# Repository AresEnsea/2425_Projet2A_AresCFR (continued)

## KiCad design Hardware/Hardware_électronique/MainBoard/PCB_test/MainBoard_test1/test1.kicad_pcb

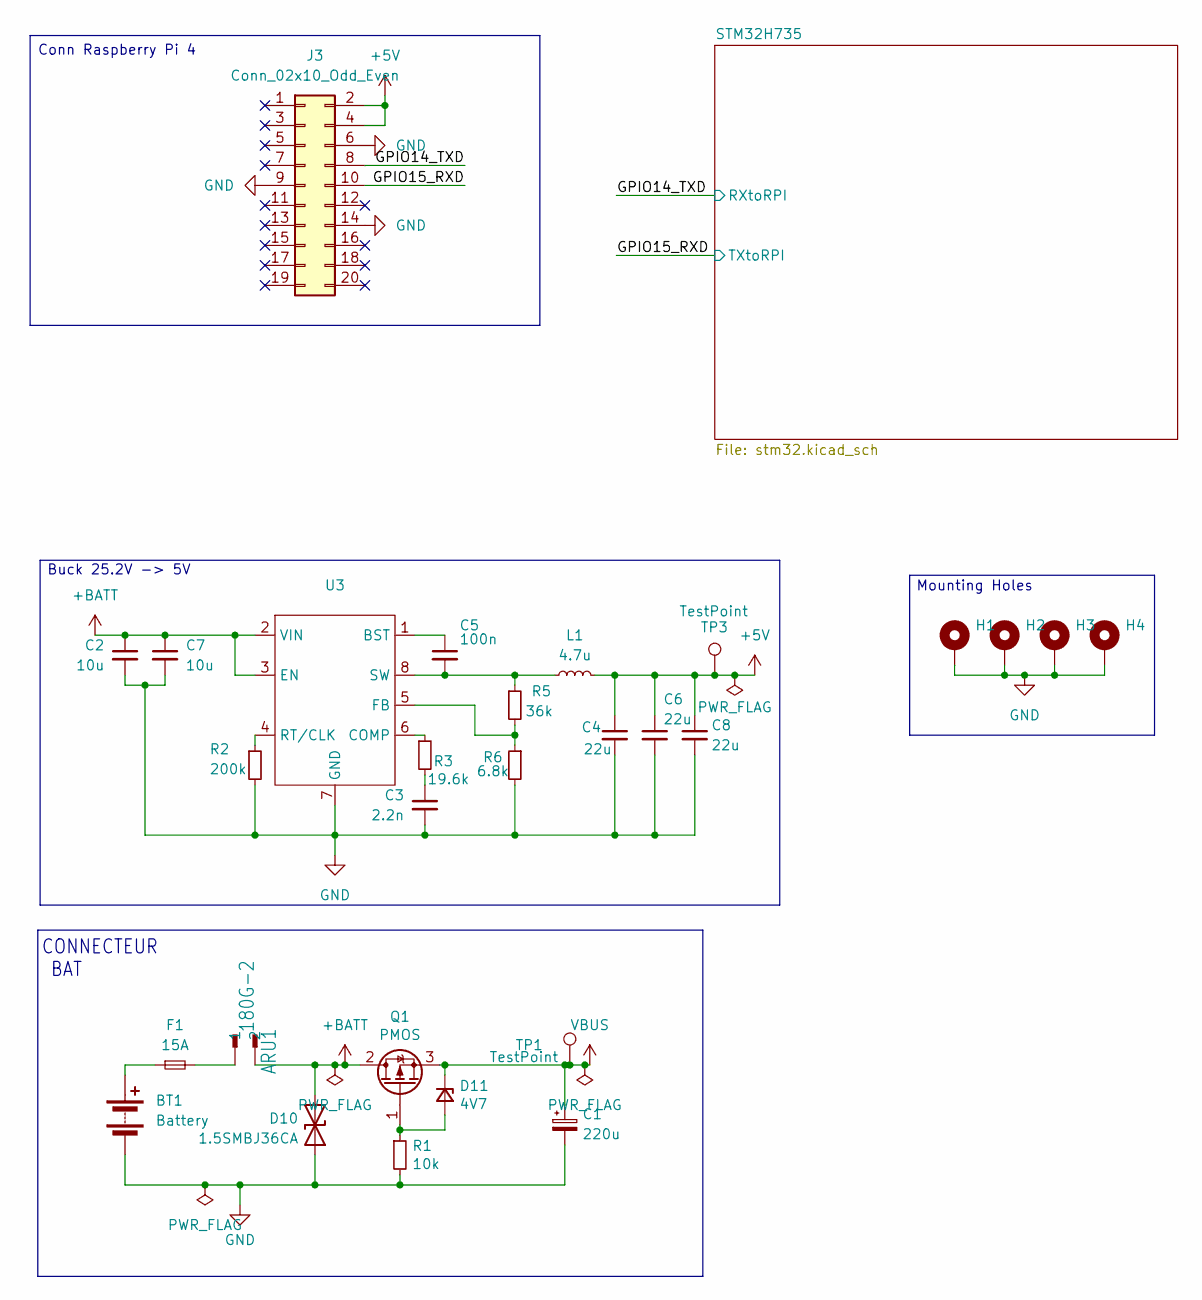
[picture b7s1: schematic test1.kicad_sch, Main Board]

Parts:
ARU1: 180G-2
BT1: Battery; AMASS_XT60PW-F_1x02_P7.20mm_Horizontal
C1: 220u; CP_Elec_10x10.5
C2, C7: 10u; C_0805_2012Metric
C3: 2.2n; C_0402_1005Metric
C4, C6, C8: 22u; C_0402_1005Metric
C5: 100n; C_0402_1005Metric
D10: 1.5SMBJ36CA; D_SMB; Mouser Part Number 652-1.5SMBJ36CA-H
D11: 4V7; D_0603_1608Metric; Mouser Part Number 771-BZX84J-C4V7115
F1: 15A; Fuse_1206_3216Metric
H1, H2, H3, H4: MountingHole_Pad; MountingHole_2.7mm_M2.5
J3: Conn_02x10_Odd_Even; PinSocket_2x10_P2.54mm_Vertical
L1: 4.7u; PA5432.472NLT; MPN 74404084220
Q1: PMOS; MOS_WDFN8; Mouser Part Number 863-NTTFS015P03P8ZWG
R1: 10k; R_0402_1005Metric
R2: 200k; R_0402_1005Metric
R3: 19.6k; R_0402_1005Metric
R5: 36k; R_0402_1005Metric
R6: 6.8k; R_0402_1005Metric
TP1, TP3: TestPoint; TestPoint_Pad_D2.0mm
U3: SOIC-8-1EP_3.9x4.9mm_P1.27mm_EP2.95x4.9mm_Mask2.71x3.4mm

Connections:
+5V: C4.1, C6.1, C8.1, J3.2, J3.4, L1.2, TP3.1; also elsewhere on the board
+BATT: ARU1.2, C2.1, C7.1, D10.2 (A2), Q1.2 (D), U3.2 (VIN), U3.3 (EN)
/GPIO14_TXD: J3.8; also elsewhere on the board
/GPIO15_RXD: J3.10; also elsewhere on the board
GND: BT1.2 (-), C1.2, C2.2, C3.2, C4.2, C6.2, C7.2, C8.2, D10.1 (A1), H1.1, H2.1, H3.1, H4.1, J3.6, J3.9, J3.14, R1.2, R2.2, R6.2, U3.7 (GND), U3.9 (EPad); also elsewhere on the board
unnamed: ARU1.1, F1.2
unnamed: BT1.1 (+), F1.1
unnamed: C3.1, R3.2
unnamed: D11.2 (A), Q1.1 (G), R1.1
unnamed: C5.1, U3.1 (BST)
unnamed: R3.1, U3.6 (COMP)
unnamed: R5.2, R6.1, U3.5 (FB)
unnamed: R2.1, U3.4 (RT/CLK)
unnamed: C5.2, L1.1, R5.1, U3.8 (SW)
VBUS: C1.1, D11.1 (K), Q1.3 (S), TP1.1; also elsewhere on the board

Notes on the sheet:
Conn Raspberry Pi 4
CONNECTEUR BAT
Buck 25.2V -> 5V
Mounting Holes

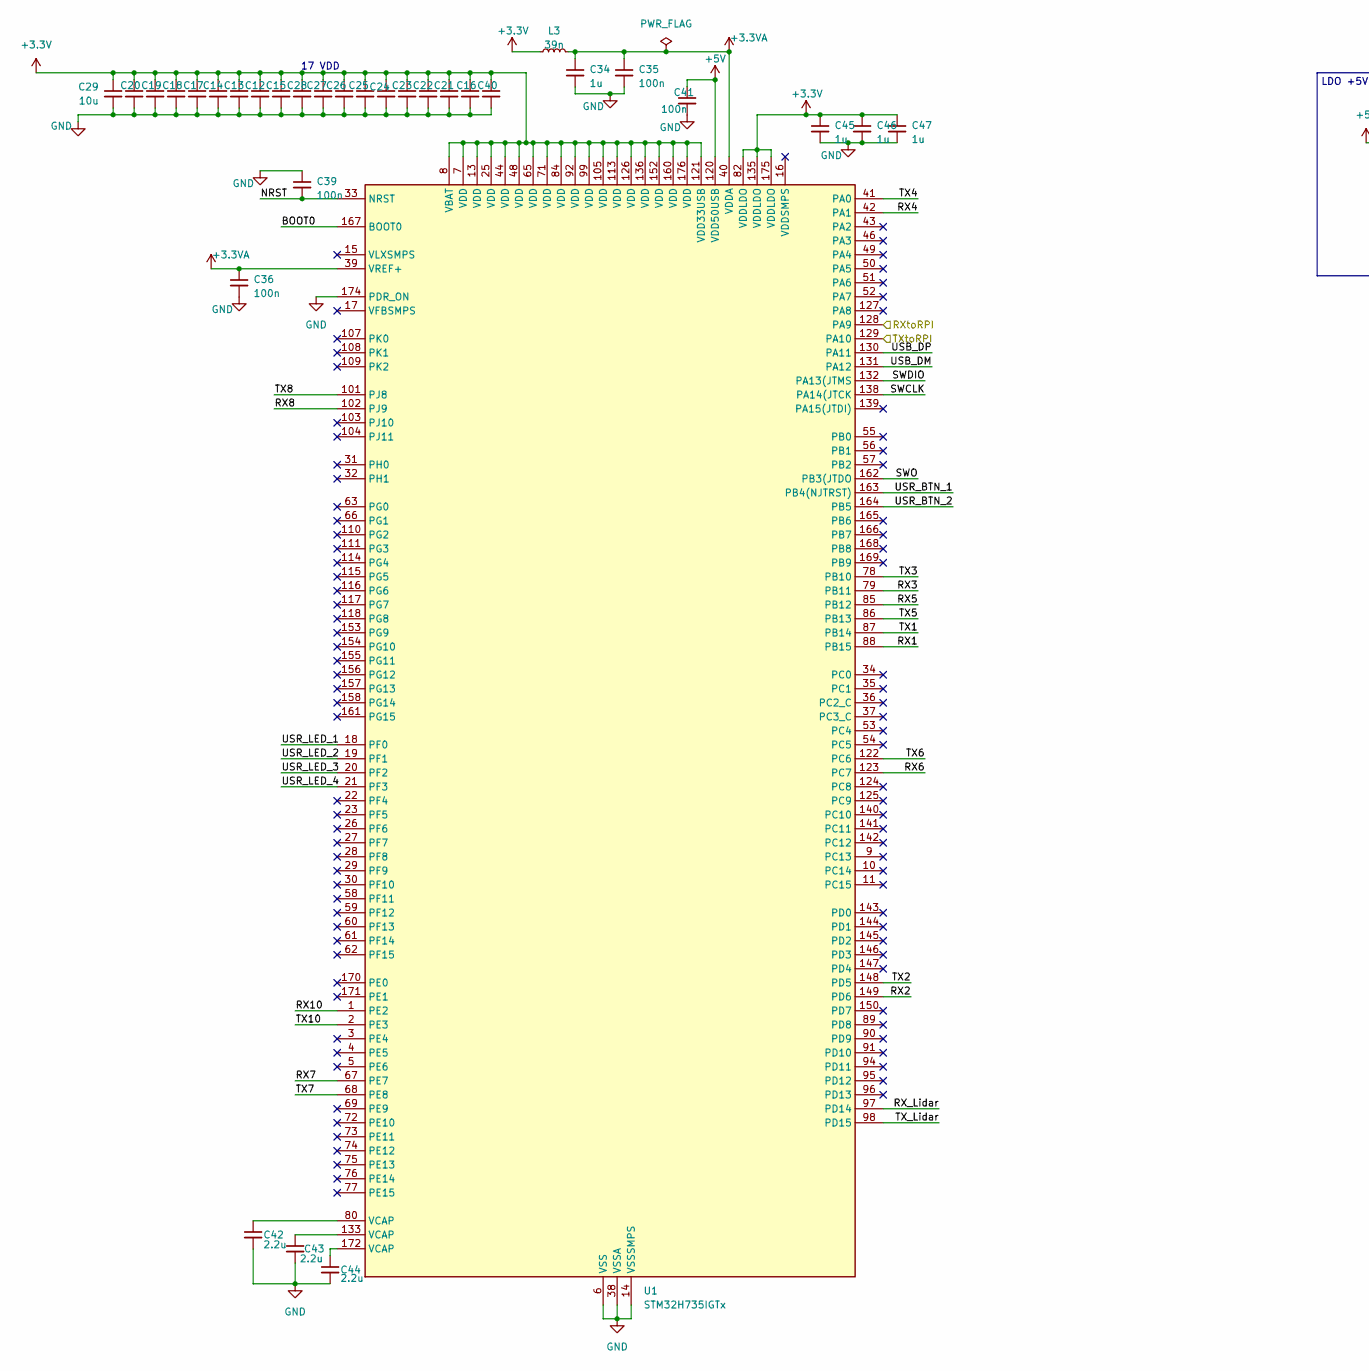
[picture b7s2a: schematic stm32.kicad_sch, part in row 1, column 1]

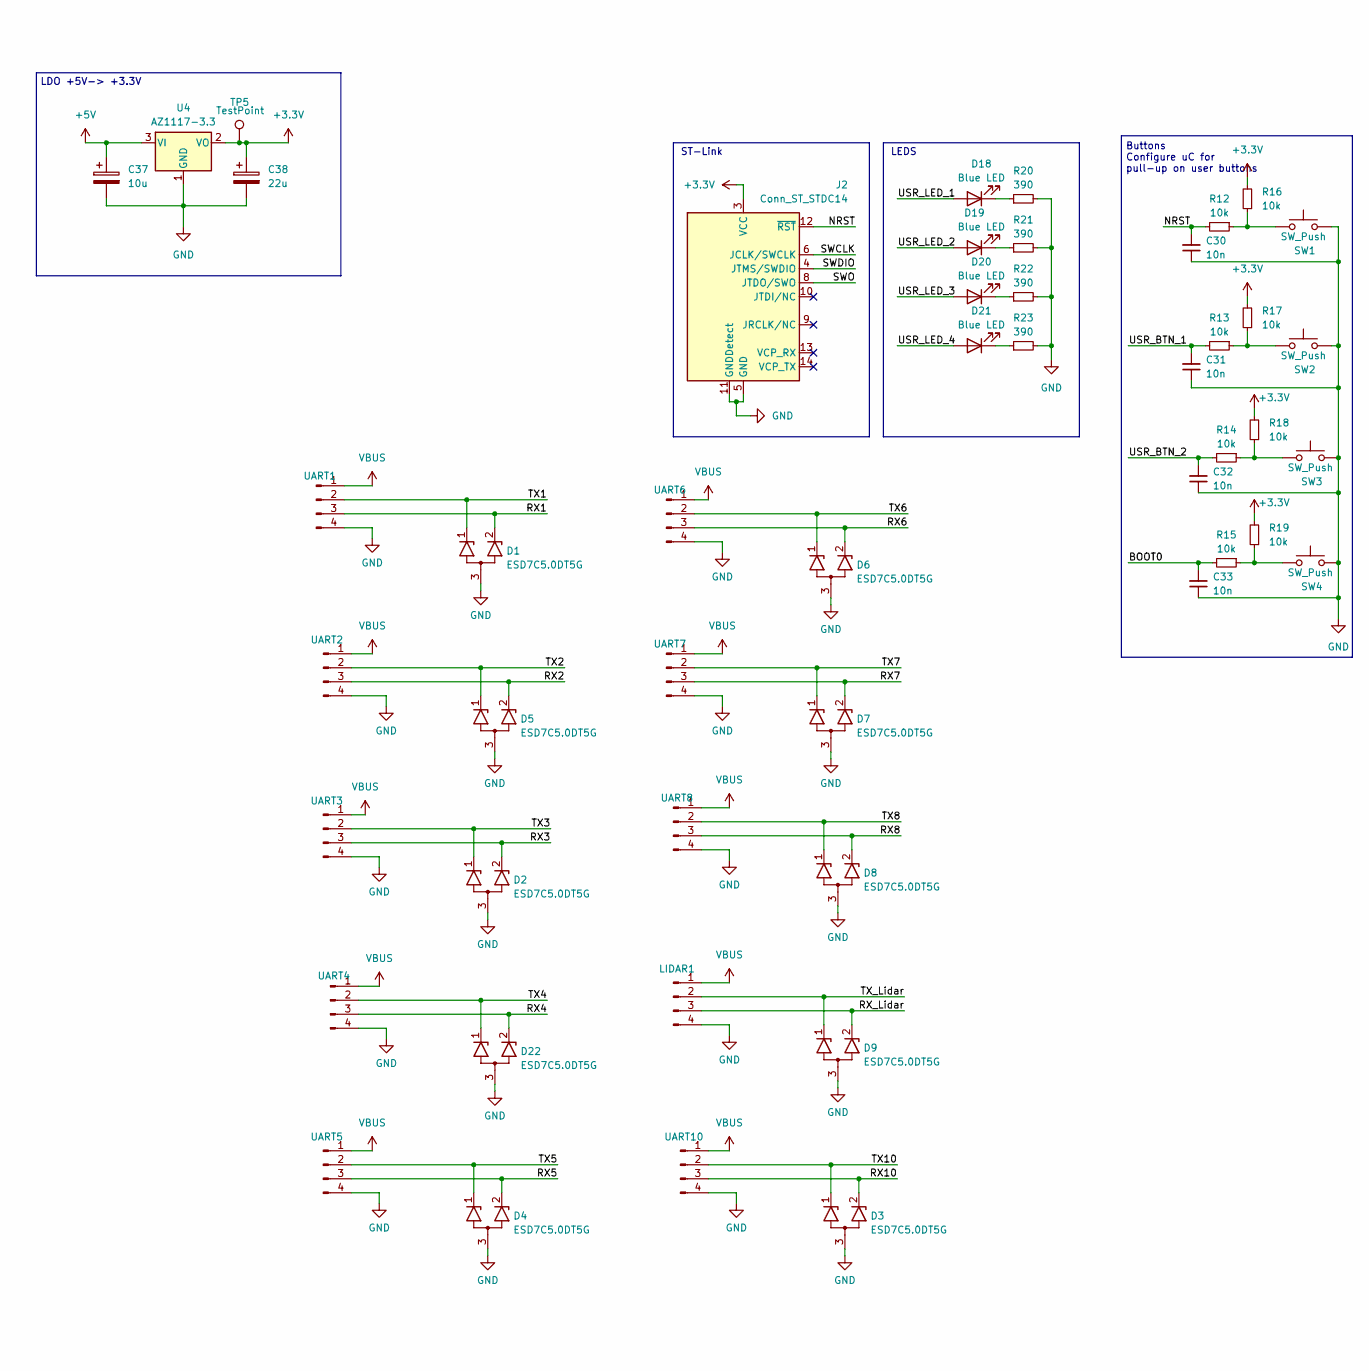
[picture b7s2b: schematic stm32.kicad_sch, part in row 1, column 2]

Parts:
C12, C13, C14, C15, C16, C17, C18, C19, C20, C21, C22, C23, C24, C25, C26, C27, C28, C40: 100n; C_0402_1005Metric_Pad0.74x0.62mm_HandSolder
C29: 10u; C_0603_1608Metric_Pad1.08x0.95mm_HandSolder
C30, C31, C32, C33: 10n; C_0402_1005Metric
C34: 1u; C_0603_1608Metric_Pad1.08x0.95mm_HandSolder
C35, C36, C39, C41: 100n; C_0402_1005Metric
C37: 10u; C_0805_2012Metric_Pad1.18x1.45mm_HandSolder
C38: 22u; C_0805_2012Metric_Pad1.18x1.45mm_HandSolder
C42, C43, C44: 2.2u; C_0402_1005Metric_Pad0.74x0.62mm_HandSolder
C45, C46, C47: 1u; C_0402_1005Metric_Pad0.74x0.62mm_HandSolder
D1, D2, D3, D4, D5, D6, D7, D8, D9, D22: ESD7C5.0DT5G; SOT-416; Mouser Part Number 863-ESD7C5.0DT5G
D18, D19, D20, D21: Blue LED; LED_0603_1608Metric
J2: Conn_ST_STDC14; PinHeader_2x07_P1.27mm_Vertical_SMD
L3: 39n; L_0603_1608Metric
LIDAR1: Conn_01x04_Male; JST_EH_B4B-EH-A_1x04_P2.50mm_Vertical
R12, R13, R14, R15, R16, R17, R18, R19: 10k; R_0402_1005Metric
R20, R21, R22, R23: 390; R_0402_1005Metric
SW1, SW2, SW3, SW4: SW_Push; 435451019820
TP5: TestPoint; TestPoint_Pad_D2.0mm
U1: STM32H735IGTx; LQFP-176_24x24mm_P0.5mm
U4: AZ1117-3.3; SOT-223-3_TabPin2
UART1, UART2, UART3, UART4, UART5, UART6, UART7, UART8, UART10: Conn_01x04_Male; JST_EH_B4B-EH-A_1x04_P2.50mm_Vertical

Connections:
+3.3V: C12.1, C13.1, C14.1, C15.1, C16.1, C17.1, C18.1, C19.1, C20.1, C21.1, C22.1, C23.1, C24.1, C25.1, C26.1, C27.1, C28.1, C29.1, C38.1, C40.1, C45.1, C46.1, C47.1, J2.3 (VCC), L3.1, R16.2, R17.2, R18.2, R19.2, TP5.1, U1.7 (VDD), U1.8 (VBAT), U1.13 (VDD), U1.25 (VDD), U1.44 (VDD), U1.48 (VDD), U1.65 (VDD), U1.71 (VDD), U1.82 (VDDLDO), U1.84 (VDD), U1.92 (VDD), U1.99 (VDD), U1.105 (VDD), U1.113 (VDD), U1.121 (VDD33USB), U1.126 (VDD), U1.135 (VDDLDO), U1.136 (VDD), U1.152 (VDD), U1.160 (VDD), U1.175 (VDDLDO), U1.176 (VDD), U4.2 (VO)
+3.3VA: C34.1, C35.1, C36.1, L3.2, U1.39 (VREF+), U1.40 (VDDA)
+5V: C37.1, C41.1, U1.120 (VDD50USB), U4.3 (VI); also elsewhere on the board
/GPIO14_TXD: U1.128 (PA9); also elsewhere on the board
/GPIO15_RXD: U1.129 (PA10); also elsewhere on the board
/STM32H735/BOOT0: C33.2, R15.2, U1.167 (BOOT0)
/STM32H735/NRST: C30.2, C39.2, J2.12 (~RST), R12.2, U1.33 (NRST)
/STM32H735/RX1: D1.2 (K2), U1.88 (PB15), UART1.3
/STM32H735/RX2: D5.2 (K2), U1.149 (PD6), UART2.3
/STM32H735/RX3: D2.2 (K2), U1.79 (PB11), UART3.3
/STM32H735/RX4: D22.2 (K2), U1.42 (PA1), UART4.3
/STM32H735/RX5: D4.2 (K2), U1.85 (PB12), UART5.3
/STM32H735/RX6: D6.2 (K2), U1.123 (PC7), UART6.3
/STM32H735/RX7: D7.2 (K2), U1.67 (PE7), UART7.3
/STM32H735/RX8: D8.2 (K2), U1.102 (PJ9), UART8.3
/STM32H735/RX10: D3.2 (K2), U1.1 (PE2), UART10.3
/STM32H735/RX_Lidar: D9.2 (K2), LIDAR1.3, U1.97 (PD14)
/STM32H735/SWCLK: J2.6 (JCLK/SWCLK), U1.138 (PA14(JTCK)
/STM32H735/SWDIO: J2.4 (JTMS/SWDIO), U1.132 (PA13(JTMS)
/STM32H735/SWO: J2.8 (JTDO/SWO), U1.162 (PB3(JTDO)
/STM32H735/TX1: D1.1 (K1), U1.87 (PB14), UART1.2
/STM32H735/TX2: D5.1 (K1), U1.148 (PD5), UART2.2
/STM32H735/TX3: D2.1 (K1), U1.78 (PB10), UART3.2
/STM32H735/TX4: D22.1 (K1), U1.41 (PA0), UART4.2
/STM32H735/TX5: D4.1 (K1), U1.86 (PB13), UART5.2
/STM32H735/TX6: D6.1 (K1), U1.122 (PC6), UART6.2
/STM32H735/TX7: D7.1 (K1), U1.68 (PE8), UART7.2
/STM32H735/TX8: D8.1 (K1), U1.101 (PJ8), UART8.2
/STM32H735/TX10: D3.1 (K1), U1.2 (PE3), UART10.2
/STM32H735/TX_Lidar: D9.1 (K1), LIDAR1.2, U1.98 (PD15)
/STM32H735/USB_DM: U1.131 (PA12)
/STM32H735/USB_DP: U1.130 (PA11)
/STM32H735/USR_BTN_1: C31.2, R13.2, U1.163 (PB4(NJTRST))
/STM32H735/USR_BTN_2: C32.2, R14.2, U1.164 (PB5)
/STM32H735/USR_LED_1: D18.2 (A), U1.18 (PF0)
/STM32H735/USR_LED_2: D19.2 (A), U1.19 (PF1)
/STM32H735/USR_LED_3: D20.2 (A), U1.20 (PF2)
/STM32H735/USR_LED_4: D21.2 (A), U1.21 (PF3)
GND: C12.2, C13.2, C14.2, C15.2, C16.2, C17.2, C18.2, C19.2, C20.2, C21.2, C22.2, C23.2, C24.2, C25.2, C26.2, C27.2, C28.2, C29.2, C30.1, C31.1, C32.1, C33.1, C34.2, C35.2, C36.2, C37.2, C38.2, C39.1, C40.2, C41.2, C42.2, C43.2, C44.2, C45.2, C46.2, C47.2, D1.3 (A), D2.3 (A), D3.3 (A), D4.3 (A), D5.3 (A), D6.3 (A), D7.3 (A), D8.3 (A), D9.3 (A), D22.3 (A), J2.5 (GND), J2.7 (GND), J2.11 (GNDDetect), LIDAR1.4, R20.2, R21.2, R22.2, R23.2, SW1.2, SW2.2, SW3.2, SW4.2, U1.6 (VSS), U1.12 (VSS), U1.14 (VSSSMPS), U1.24 (VSS), U1.38 (VSSA), U1.45 (VSS), U1.47 (VSS), U1.64 (VSS), U1.70 (VSS), U1.81 (VSS), U1.83 (VSS), U1.93 (VSS), U1.100 (VSS), U1.106 (VSS), U1.112 (VSS), U1.119 (VSS), U1.134 (VSS), U1.137 (VSS), U1.151 (VSS), U1.159 (VSS), U1.173 (VSS), U1.174 (PDR_ON), U4.1 (GND), UART1.4, UART2.4, UART3.4, UART4.4, UART5.4, UART6.4, UART7.4, UART8.4, UART10.4; also elsewhere on the board
unnamed: C42.1, U1.80 (VCAP)
unnamed: C43.1, U1.133 (VCAP)
unnamed: C44.1, U1.172 (VCAP)
unnamed: D18.1 (K), R20.1
unnamed: D19.1 (K), R21.1
unnamed: D20.1 (K), R22.1
unnamed: D21.1 (K), R23.1
unnamed: R12.1, R16.1, SW1.1
unnamed: R13.1, R17.1, SW2.1
unnamed: R14.1, R18.1, SW3.1
unnamed: R15.1, R19.1, SW4.1
VBUS: LIDAR1.1, UART1.1, UART2.1, UART3.1, UART4.1, UART5.1, UART6.1, UART7.1, UART8.1, UART10.1; also elsewhere on the board

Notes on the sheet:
LDO +5V-> +3.3V
LEDS
17 VDD
Buttons Configure uC for pull-up on user buttons
ST-Link

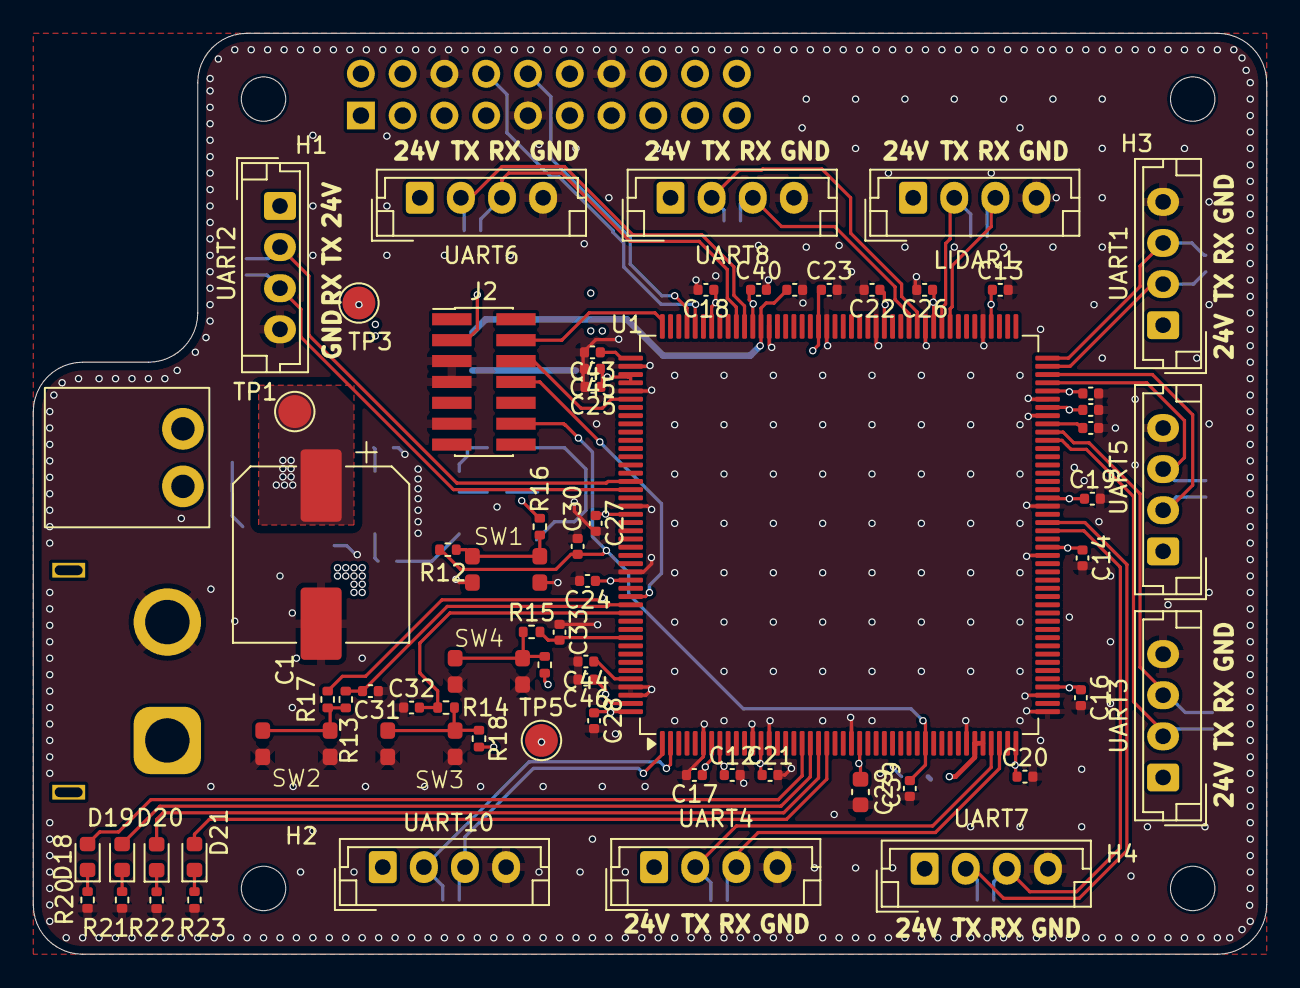
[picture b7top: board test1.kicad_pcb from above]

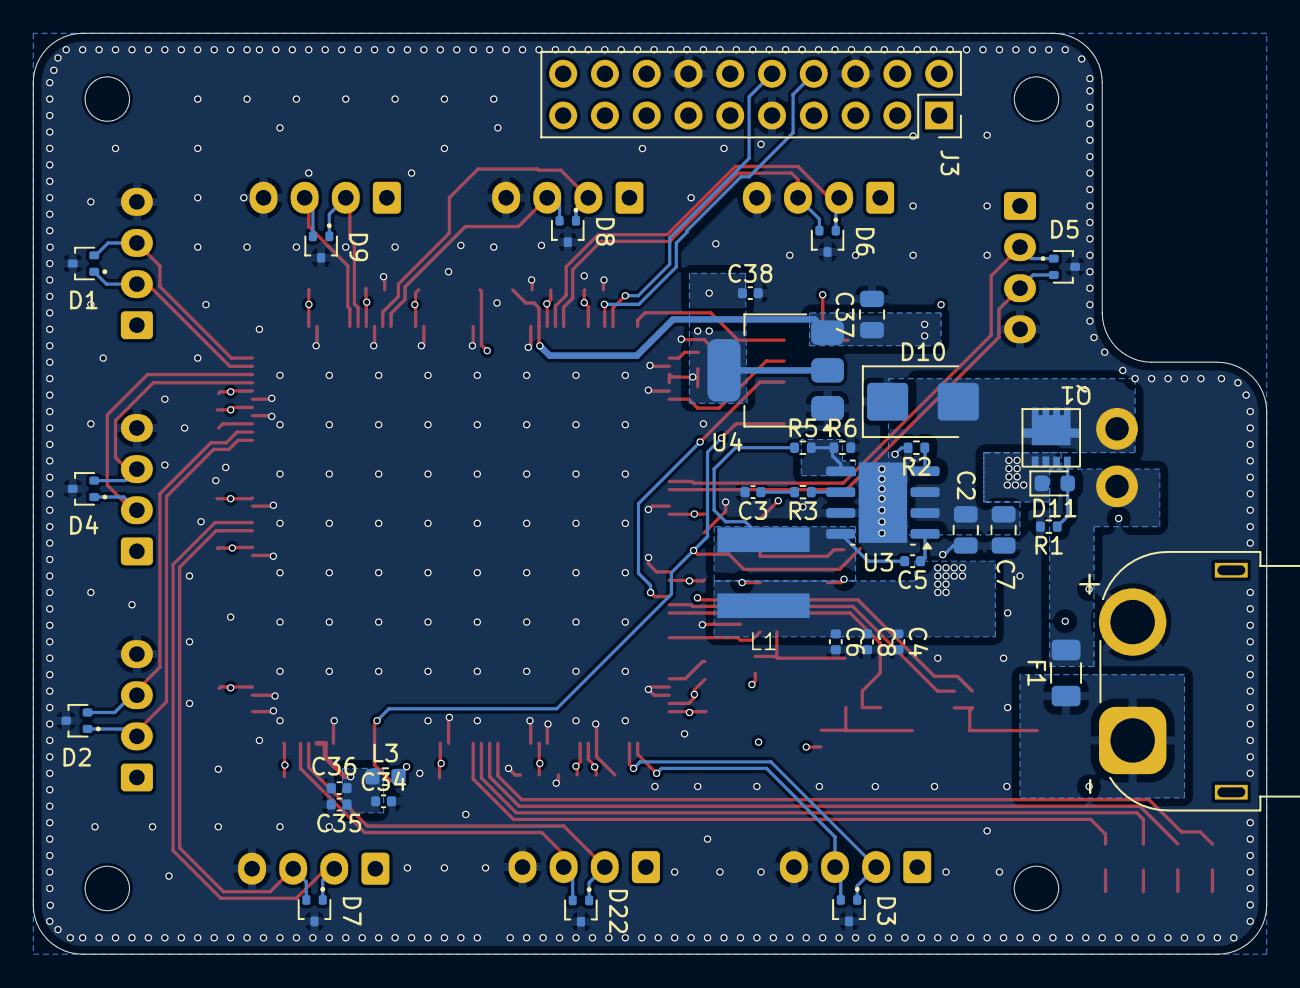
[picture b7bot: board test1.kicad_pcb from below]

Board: 4 copper layers, 75.0 x 56.0 mm, 109 parts (37 on the bottom side), 59 nets.

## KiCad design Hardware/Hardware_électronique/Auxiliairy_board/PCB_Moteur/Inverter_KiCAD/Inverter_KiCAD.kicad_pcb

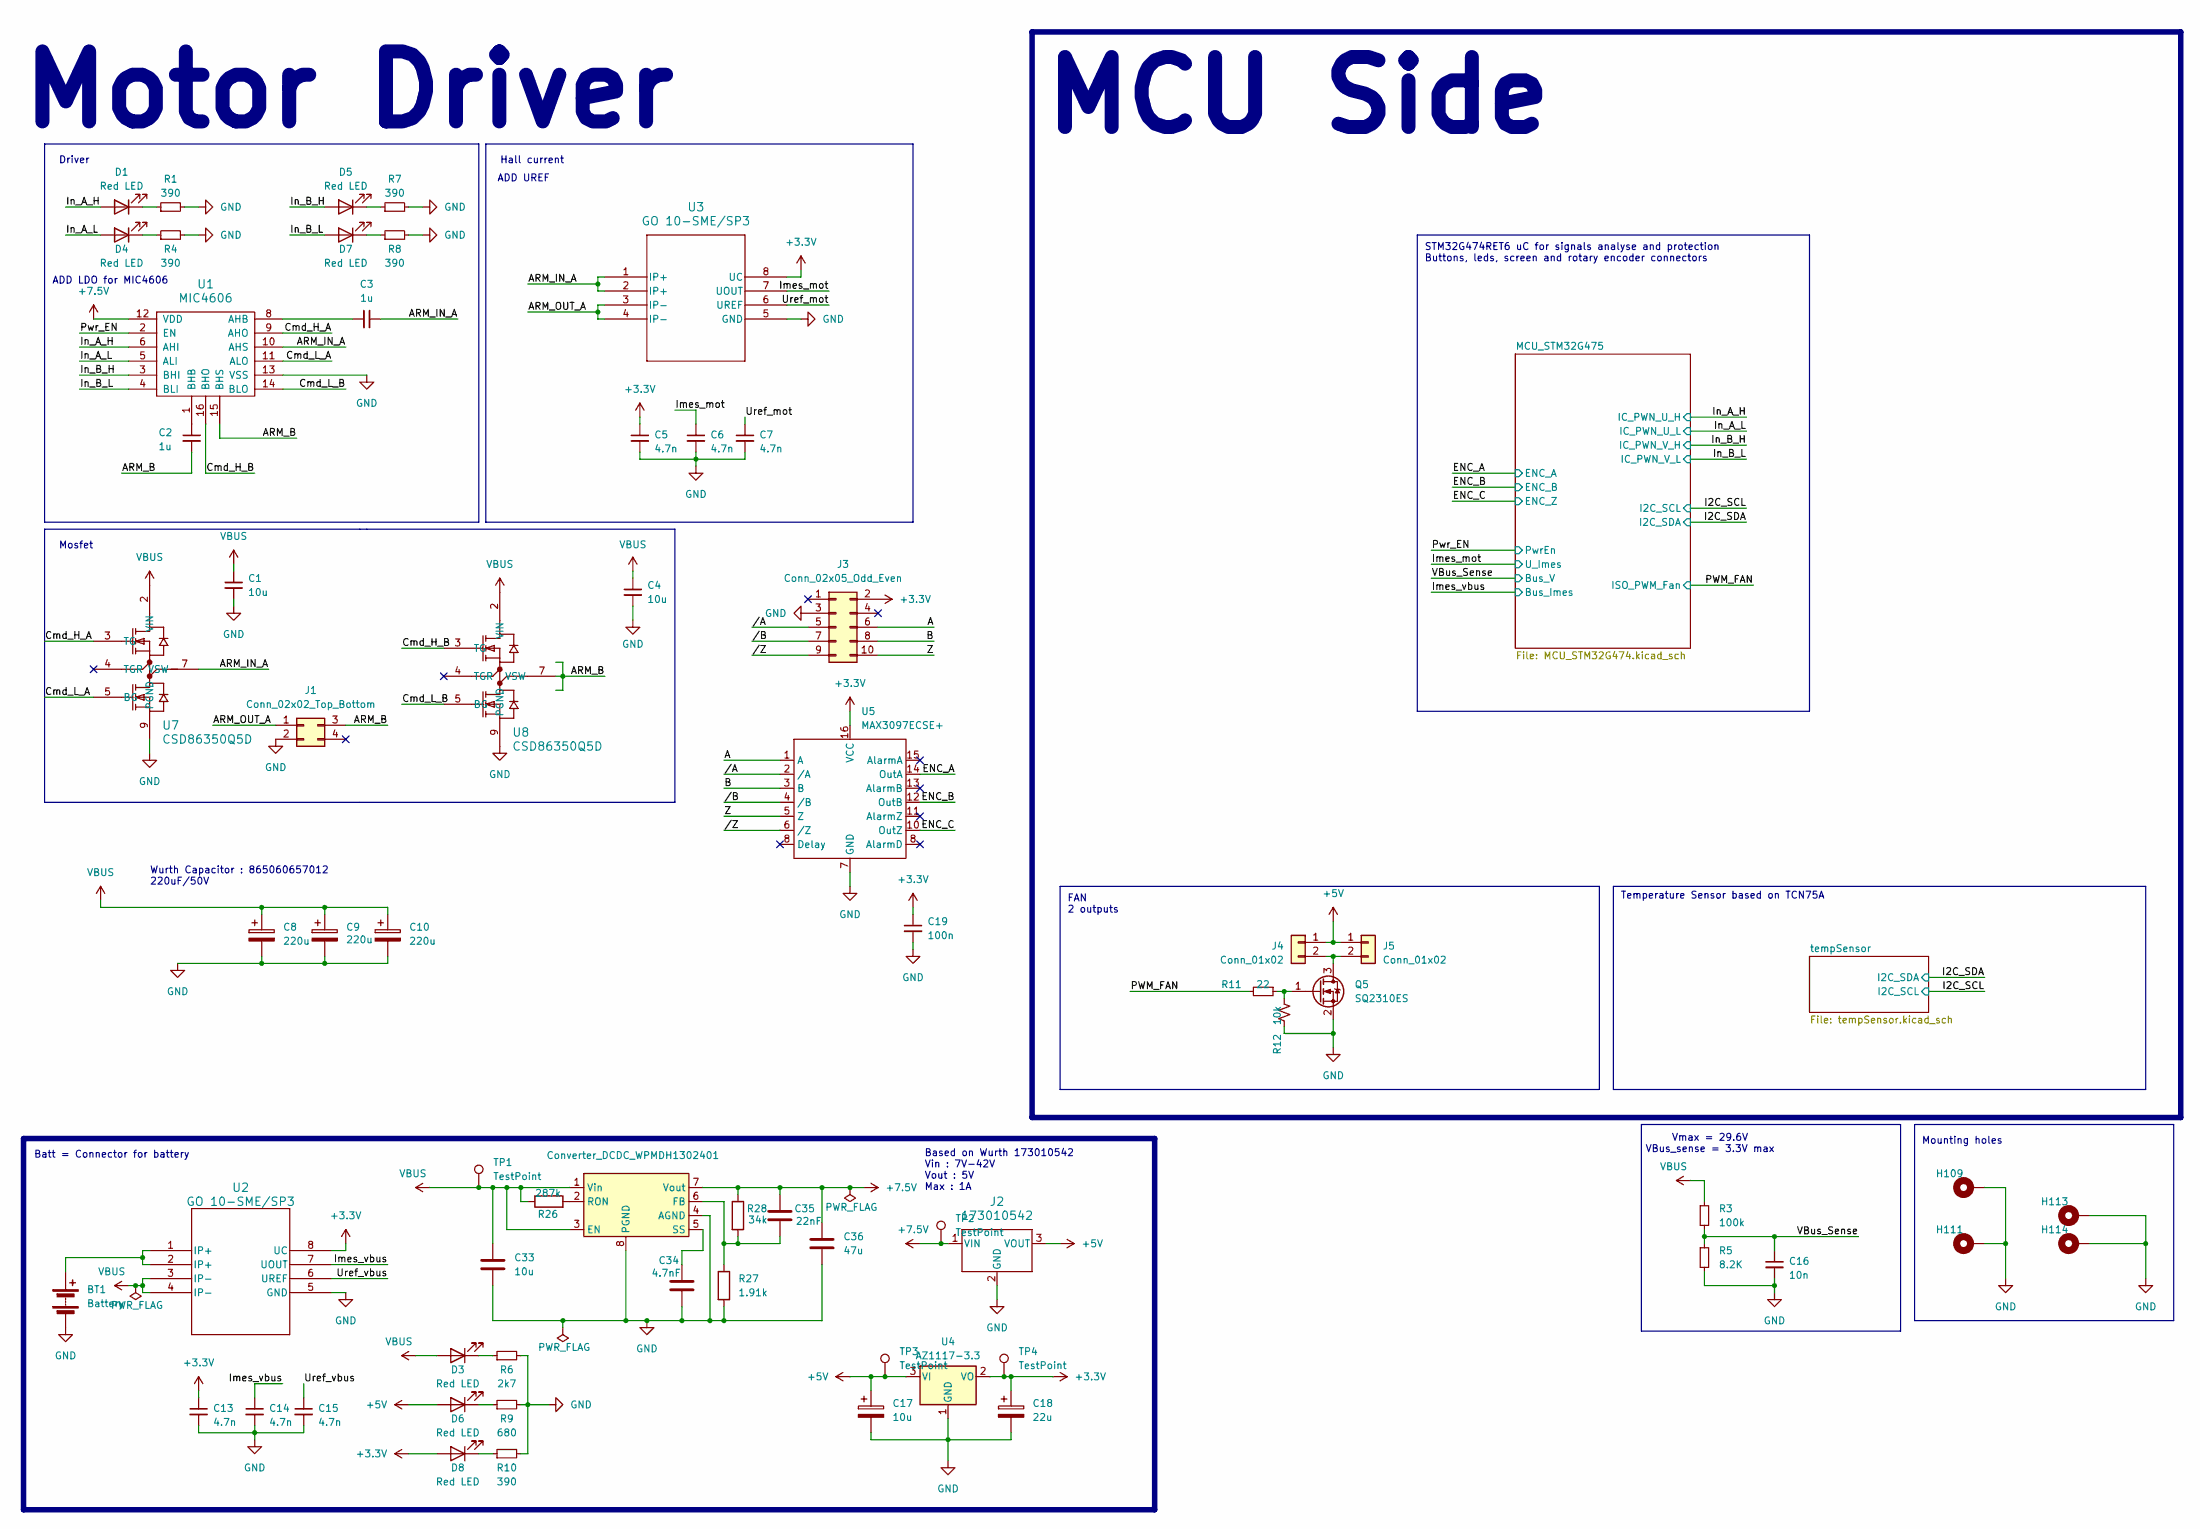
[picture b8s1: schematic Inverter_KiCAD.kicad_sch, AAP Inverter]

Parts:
BT1: Battery; AMASS_XT60-M_1x02_P7.20mm_Vertical
C1, C4, C17, C33: 10u; C_0603_1608Metric_Pad1.08x0.95mm_HandSolder
C2, C3: 1u; C_0603_1608Metric_Pad1.08x0.95mm_HandSolder
C5, C6, C7, C13, C14, C15: 4.7n; C_0402_1005Metric
C8, C9, C10: 220u; CP_Elec_10x10.5
C16: 10n; C_0402_1005Metric
C18: 22u; C_0603_1608Metric_Pad1.08x0.95mm_HandSolder
C19: 100n; C_0402_1005Metric
C34: 4.7nF; C_0402_1005Metric_Pad0.74x0.62mm_HandSolder
C35: 22nF; C_0402_1005Metric
C36: 47u; C_0805_2012Metric
Converter_DCDC_WPMDH1302401: TO-263-7_TabPin8
D1, D3, D4, D5, D6, D7, D8: Red LED; LED_0603_1608Metric
H109, H111, H113, H114: MountingHole_Pad; MountingHole_3.2mm_M3_Pad_Via
J1: Conn_02x02_Top_Bottom; Molex_Micro-Fit_3.0_43045-0400_2x02_P3.00mm_Horizontal
J2: 173010542; PinHeader_1x03_P2.54mm_Vertical; MPN 173010542
J3: Conn_02x05_Odd_Even; PinHeader_2x05_P2.54mm_Vertical
J4, J5: Conn_01x02; JST_XH_B2B-XH-A_1x02_P2.50mm_Vertical
Q5: SQ2310ES; SOT-23
R1, R4, R7, R8, R10: 390; R_0402_1005Metric
R3: 100k; R_0402_1005Metric
R5: 8.2K; R_0402_1005Metric
R6: 2k7; R_0402_1005Metric
R9: 680; R_0402_1005Metric
R11: 22; R_0402_1005Metric
R12: 10k; R_0402_1005Metric
R26: 287k; R_0402_1005Metric
R27: 1.91k; R_0402_1005Metric
R28: 34k; R_0402_1005Metric
TP1, TP2, TP3, TP4: TestPoint; TestPoint_Pad_D2.0mm
U1: MIC4606; TSSOP-16-1EP_4.4x5mm_P0.65mm_EP3x3mm
U2, U3: GO 10-SME/SP3; SOIC8-GO-SME&slash_SP3_LEM
U4: AZ1117-3.3; SOT-223-3_TabPin2
U5: MAX3097ECSE+; SOIC-16_3.9x9.9mm_P1.27mm
U7, U8: CSD86350Q5D; DQY0008A

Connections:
+3.3V: C5.1, C13.1, C18.1, C19.1, D8.2 (A), J3.2, TP4.1, U2.8 (UC), U3.8 (UC), U4.2 (VO), U5.16 (VCC); also elsewhere on the board
+5V: C17.1, D6.2 (A), J2.3 (VOUT), J4.1, J5.1, TP3.1, U4.3 (VI); also elsewhere on the board
+7.5V: C35.1, C36.1, Converter_DCDC_WPMDH1302401.7 (Vout), J2.1 (VIN), R28.1, TP2.1, U1.12 (VDD); also elsewhere on the board
/A: J3.6, U5.1 (A)
/ARM_B: C2.2, J1.3, U1.15 (BHS), U8.6 (VSW), U8.7 (VSW), U8.8 (VSW)
/ARM_IN_A: C3.1, U1.10 (AHS), U3.1 (IP+), U3.2 (IP+), U7.6 (VSW), U7.7 (VSW), U7.8 (VSW)
/ARM_OUT_A: J1.1, U3.3 (IP-), U3.4 (IP-)
/B: J3.8, U5.3 (B)
/Cmd_H_A: U1.9 (AHO), U7.3 (TG)
/Cmd_H_B: U1.16 (BHO), U8.3 (TG)
/Cmd_L_A: U1.11 (ALO), U7.5 (BG)
/Cmd_L_B: U1.14 (BLO), U8.5 (BG)
/ENC_A: U5.14 (OutA); also elsewhere on the board
/ENC_B: U5.12 (OutB); also elsewhere on the board
/ENC_C: U5.10 (OutZ); also elsewhere on the board
/Imes_mot: C6.1, U3.7 (UOUT); also elsewhere on the board
/Imes_vbus: C14.1, U2.7 (UOUT); also elsewhere on the board
/In_A_H: D1.2 (A), U1.6 (AHI); also elsewhere on the board
/In_A_L: D4.2 (A), U1.5 (ALI); also elsewhere on the board
/In_B_H: D5.2 (A), U1.3 (BHI); also elsewhere on the board
/In_B_L: D7.2 (A), U1.4 (BLI); also elsewhere on the board
/PWM_FAN: R11.2; also elsewhere on the board
/Pwr_EN: U1.2 (EN); also elsewhere on the board
/Uref_mot: C7.1, U3.6 (UREF)
/Uref_vbus: C15.1, U2.6 (UREF)
/VBus_Sense: C16.1, R3.2, R5.1; also elsewhere on the board
/Z: J3.10, U5.5 (Z)
//A: J3.5, U5.2 (/A)
//B: J3.7, U5.4 (/B)
//Z: J3.9, U5.6 (/Z)
GND: BT1.2 (-), C1.2, C4.2, C5.2, C6.2, C7.2, C8.2, C9.2, C10.2, C13.2, C14.2, C15.2, C16.2, C17.2, C18.2, C19.2, C33.2, C34.2, C36.2, Converter_DCDC_WPMDH1302401.4 (AGND), Converter_DCDC_WPMDH1302401.8 (PGND), H109.1, H111.1, H113.1, H114.1, J1.2, J2.2 (GND), J3.3, Q5.2 (S), R1.2, R4.2, R5.2, R6.2, R7.2, R8.2, R9.2, R10.2, R12.2, R27.2, U1.13 (VSS), U2.5 (GND), U3.5 (GND), U4.1 (GND), U5.7 (GND), U7.9 (PGND), U8.9 (PGND); also elsewhere on the board
unnamed: BT1.1 (+), U2.1 (IP+), U2.2 (IP+)
unnamed 48: C35.2, Converter_DCDC_WPMDH1302401.6 (FB), R27.1, R28.2; also elsewhere on the board
unnamed 49: Converter_DCDC_WPMDH1302401.2 (RON), R26.2; also elsewhere on the board
unnamed 50: C34.1, Converter_DCDC_WPMDH1302401.5 (SS); also elsewhere on the board
unnamed: D1.1 (K), R1.1
unnamed: D3.1 (K), R6.1
unnamed: D4.1 (K), R4.1
unnamed: D5.1 (K), R7.1
unnamed: D6.1 (K), R9.1
unnamed: D7.1 (K), R8.1
unnamed: D8.1 (K), R10.1
unnamed: J4.2, J5.2, Q5.3 (D)
unnamed: Q5.1 (G), R11.1, R12.1
unnamed: C3.2, U1.8 (AHB)
unnamed: C2.1, U1.1 (BHB)
VBUS: C1.1, C4.1, C8.1, C9.1, C10.1, C33.1, Converter_DCDC_WPMDH1302401.1 (Vin), Converter_DCDC_WPMDH1302401.3 (EN), D3.2 (A), R3.1, R26.1, TP1.1, U2.3 (IP-), U2.4 (IP-), U7.1 (VIN), U7.2 (VIN), U8.1 (VIN), U8.2 (VIN); also elsewhere on the board

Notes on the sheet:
ADD UREF
Temperature Sensor based on TCN75A
ADD LDO for MIC4606
STM32G474RET6 uC for signals analyse and protection Buttons, leds, screen and rotary encoder connectors
Mounting holes
Hall current
Mosfet
Vmax = 29.6V VBus_sense = 3.3V max
Wurth Capacitor : 865060657012 220uF/50V
Batt = Connector for battery
Driver
MCU Side
FAN 2 outputs
Based on Wurth 173010542 Vin : 7V-42V Vout : 5V Max : 1A
Motor Driver

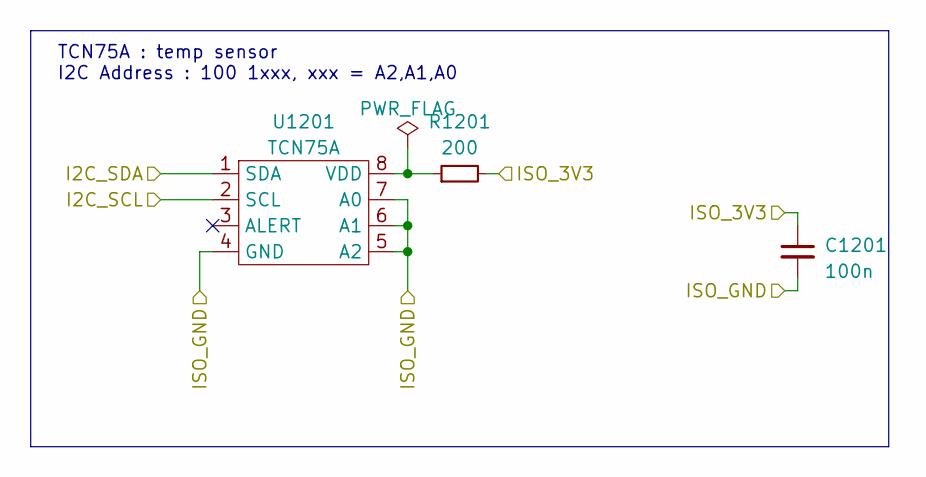
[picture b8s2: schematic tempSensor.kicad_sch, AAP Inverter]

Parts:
C1201: 100n; C_0402_1005Metric
R1201: 200; R_0402_1005Metric
U1201: TCN75A; SOIC-8_3.9x4.9mm_P1.27mm

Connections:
+3.3V: C1201.1, R1201.2; also elsewhere on the board
/I2C_SCL: U1201.2 (SCL); also elsewhere on the board
/I2C_SDA: U1201.1 (SDA); also elsewhere on the board
GND: C1201.2, U1201.4 (GND), U1201.5 (A2), U1201.6 (A1), U1201.7 (A0); also elsewhere on the board
unnamed: R1201.1, U1201.8 (VDD)

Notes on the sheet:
TCN75A : temp sensor I2C Address : 100 1xxx, xxx = A2,A1,A0
